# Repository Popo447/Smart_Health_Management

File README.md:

# Smart_Health_Management
Implementation of Sugeno Fuzzy Logic for Lifestyle and Health Management in Obese Individuals Using IoT Technology

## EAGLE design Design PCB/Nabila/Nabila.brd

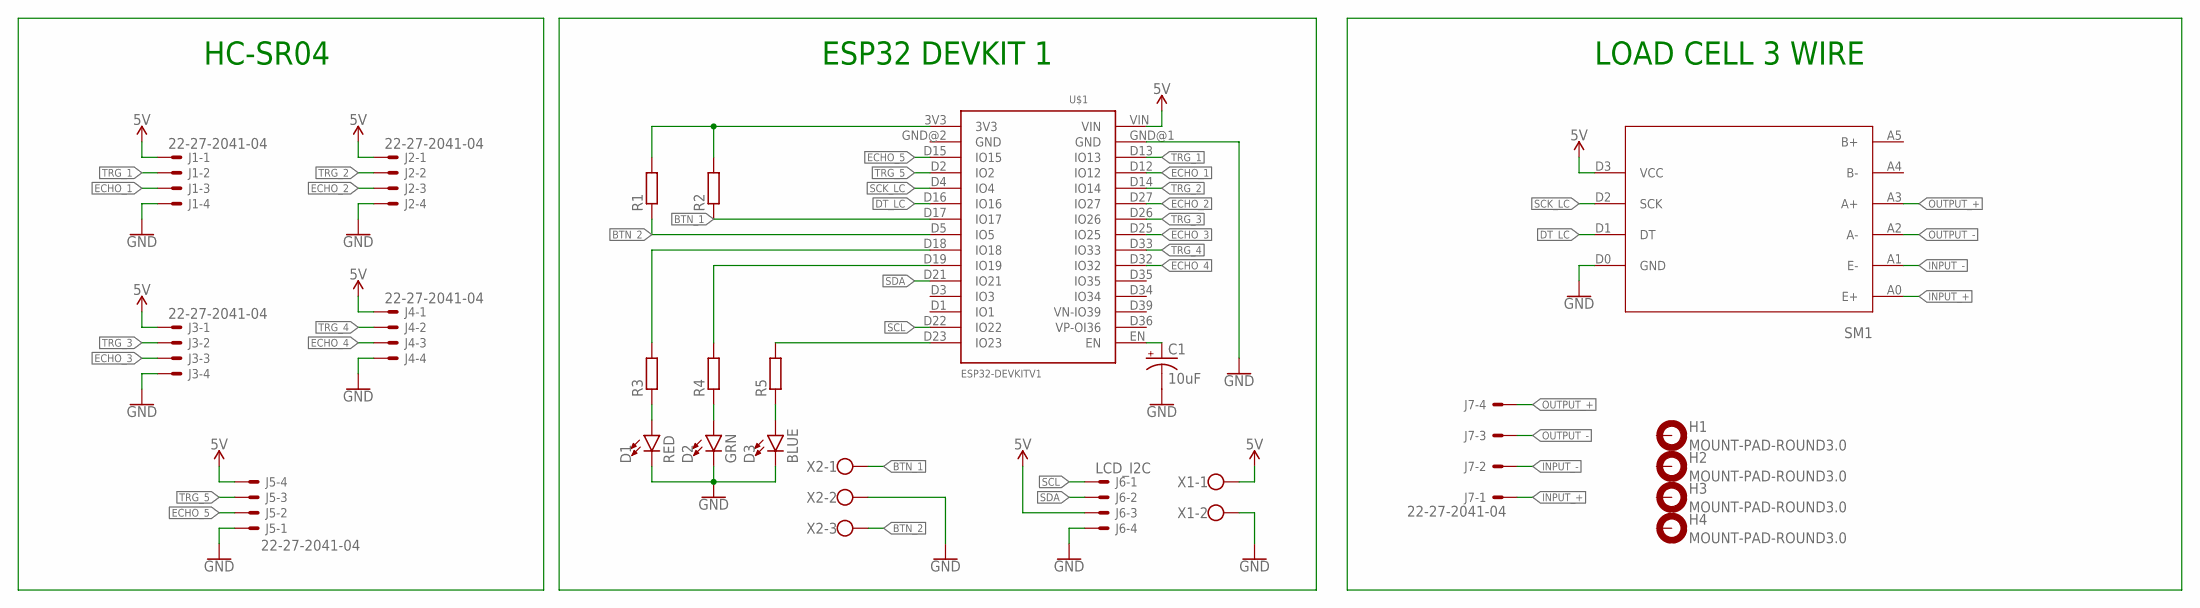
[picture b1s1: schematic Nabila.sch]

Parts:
C1: 10uF; E2-5
D1: RED; LED_5MM
D2: GRN; LED_5MM
D3: BLUE; LED_5MM
H1, H2, H3, H4: MOUNT-PAD-ROUND3.0; 3,0-PAD
J1, J2, J3, J4, J5, J7: 22-27-2041-04; 6410-04
J6: LCD_I2C; 6410-04
R1, R2, R3, R4, R5: R-EU_0207/10; 0207/10
SM1: HX711
U$1: ESP32DEVKITV1; ESP32-DEVKITV1
X1: W237-102
X2: W237-103

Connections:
5V: J1.1, J2.1, J3.1, J4.1, J5.4, J6.3, SM1.D3 (VCC), U$1.VIN, X1.1
BTN_1: R2.1, U$1.D17 (IO17), X2.1
BTN_2: R1.1, U$1.D5 (IO5), X2.3
DT_LC: SM1.D1 (DT), U$1.D16 (IO16)
ECHO_1: J1.3, U$1.D12 (IO12)
ECHO_2: J2.3, U$1.D27 (IO27)
ECHO_3: J3.3, U$1.D25 (IO25)
ECHO_4: J4.3, U$1.D32 (IO32)
ECHO_5: J5.2, U$1.D15 (IO15)
GND: C1.-, D1.K (C), D2.K (C), D3.K (C), J1.4, J2.4, J3.4, J4.4, J5.1, J6.4, SM1.D0 (GND), U$1.GND@1 (GND), X1.2, X2.2
INPUT_+: J7.1, SM1.A0 (E+)
INPUT_-: J7.2, SM1.A1 (E-)
unnamed: R1.2, R2.2, U$1.3V3
unnamed: R3.2, U$1.D18 (IO18)
unnamed: R4.2, U$1.D19 (IO19)
unnamed: R5.2, U$1.D23 (IO23)
unnamed: D1.A, R3.1
unnamed: D2.A, R4.1
unnamed: D3.A, R5.1
unnamed: C1.+, U$1.EN
OUTPUT_+: J7.4, SM1.A3 (A+)
OUTPUT_-: J7.3, SM1.A2 (A-)
SCK_LC: SM1.D2 (SCK), U$1.D4 (IO4)
SCL: J6.1, U$1.D22 (IO22)
SDA: J6.2, U$1.D21 (IO21)
TRG_1: J1.2, U$1.D13 (IO13)
TRG_2: J2.2, U$1.D14 (IO14)
TRG_3: J3.2, U$1.D26 (IO26)
TRG_4: J4.2, U$1.D33 (IO33)
TRG_5: J5.3, U$1.D2 (IO2)

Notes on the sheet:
HC-SR04
ESP32 DEVKIT 1
LOAD CELL 3 WIRE

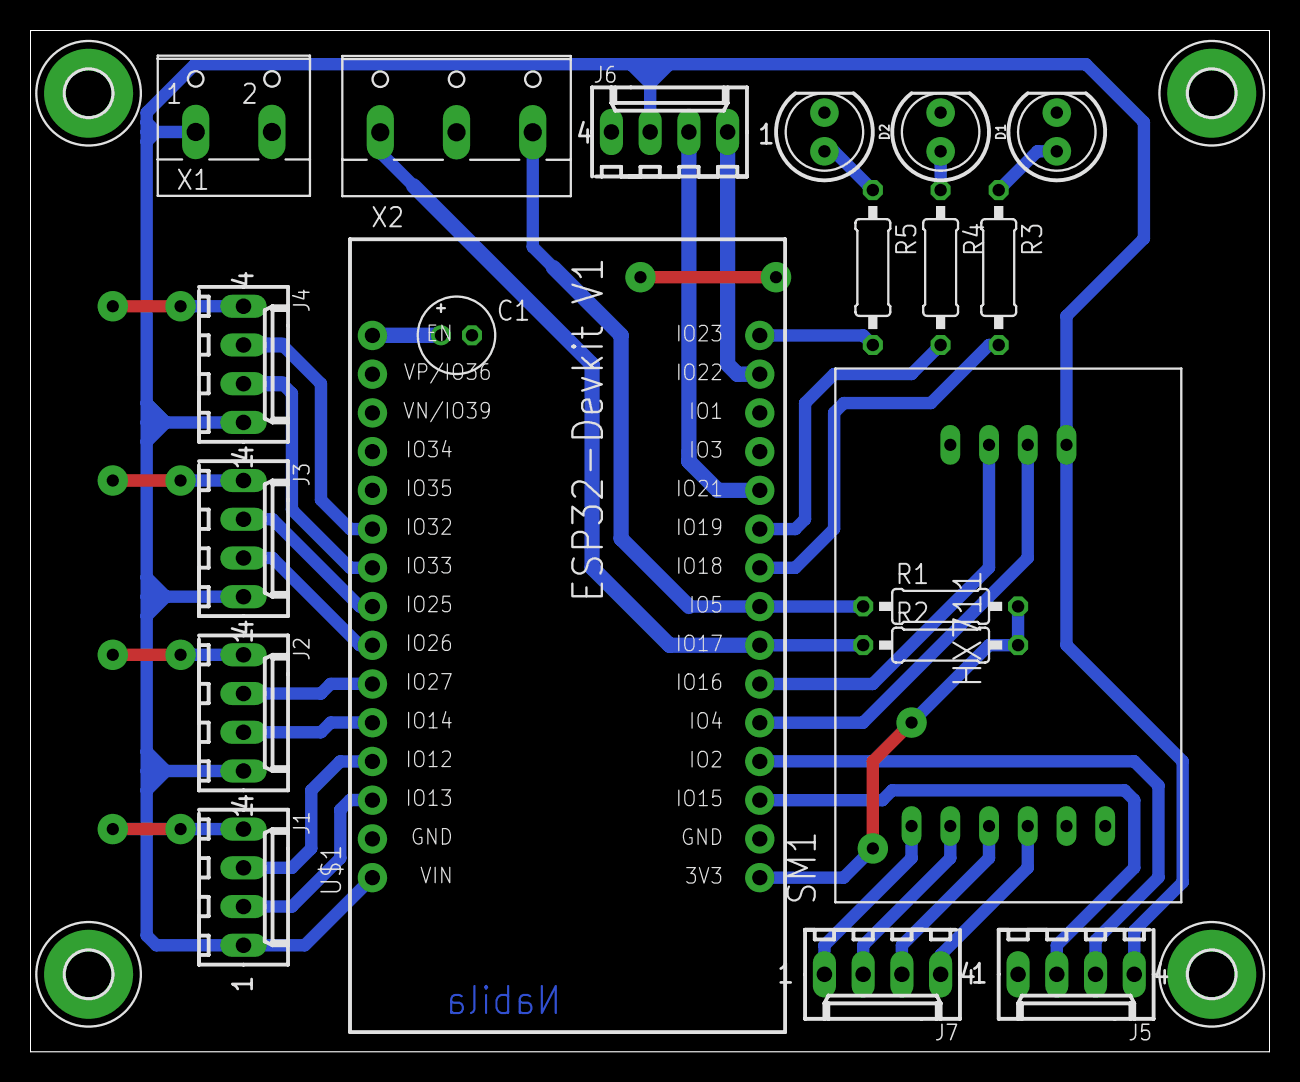
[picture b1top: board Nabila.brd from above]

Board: 2 copper layers, 81.3 x 67.0 mm, 24 parts (0 on the bottom side), 30 nets.

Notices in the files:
parts and their libraries:
1206_led: Licensing: Creative Commons ShareAlike 4.0 International - https://creativecommons.org/licenses/by-sa/4.0
